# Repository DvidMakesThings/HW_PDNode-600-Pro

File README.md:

# PDNode-600 Pro  
## High-Performance USB PD Power Distribution Unit – 10" Rackmount

## Description  
[ENERGIS](https://github.com/DvidMakesThings/HW_10-In-Rack_PDU) is the 230V managed PDU project. PDNode-600 Pro is the modular DC/USB-C sibling for setups
where mains switching is not desired, but controllable, rack-friendly power output is still needed.

The PDNode-600 is a professional-grade, 600W USB Power Delivery Unit designed specifically for compact 10-inch rack systems, targeting embedded developers, homelab enthusiasts, test benches, and smart infrastructure. It delivers regulated, high-current power across 8x independent USB-C PD outputs and 4x fixed 5V USB-A outputs.

At the core of the PDNode platform is a centralized industrial-grade 24V/25A power supply, distributing regulated DC to dedicated per-port buck or buck-boost converters. Each USB-C port is managed by an MPQ4242-AEC1 PD controller, enabling clean, autonomous negotiation of power profiles up to 20V @ 3A or 5A with eMarker cable support. All power conversion, protection, and monitoring are designed to meet high reliability and safety standards.

The PDNode-600 Pro, by contrast, is built for remote-managed racks and headless environments, featuring Ethernet connectivity, a clean web-based UI, SNMP integration, and firmware updates via USB-C. Doing this by using [BladeCore-M54E](https://github.com/DvidMakesThings/HW_BladeCore-M54E)

## Web UI sneak peek

Interactive playground (dummy UI):
- https://dvidmakesthings.github.io/HW_PDNode-600-Pro/playground/

## Project timeline estimation

Status legend: ✅ Completed · 🟠 Ongoing · 🔵 Planned

| #  | Milestone                                      | Planned Start | Planned End | Status       | Notes |
|:--:|------------------------------------------------|---------------|-------------|--------------|-------|
| 1  | Architecture definition                        | 12-2025       | 01-2026     | ✅ Completed |       |
| 2  | Baseboard PCB design                           | 15-02-2026    | TBD         | ✅ Completed |       |
| 3  | PD card PCB design                             | 25-02-2026    | TBD         | ✅ Completed |       |
| 4  | Documentation                                  | 12-2025       | 2026.12     | 🟠 Ongoing   |       |
| 5  | PCB ordering                                   | 01-03-2026    | 31-03-2026  | ✅ Completed | Waiting for arrival |
| 6  | Prototyping and hardware bring-up              | 03-2026       | 30-04-2026  | 🟠 Ongoing   |       |
| 7  | Firmware bring-up (slot scan, mux, PD iface)   | 06-2026       | 11-2026     | 🔵 Planned   |       |
| 8  | Telemetry and status reporting                 | 06-2026       | 11-2026     | 🔵 Planned   |       |
| 9  | Validation (load, thermal, long-run)           | 06-2026       | 11-2026     | 🔵 Planned   |       |
| 10 | Integration and polishing                      | 06-2026       | 11-2026     | 🔵 Planned   |       |
| 11 | Release package and final docs                 | 11-2026       | 12-2026     | 🔵 Planned   |       |

## Specifications 

### Input
- **Input voltage:** 230 VAC, max 4A 
- **System topology:** 24V distribution on the baseboard, per-slot conversion on PD cards

### Output (per PD card / per slot)
- **8x independent USB-C PD source**:
  - 5V 3A (5A only with 5A e-marked cable)
  - 9V 3A (5A only with 5A e-marked cable)
  - 12V 3A (5A only with 5A e-marked cable)
  - 15V 3A (5A only with 5A e-marked cable)
  - 20V 3A (5A only with 5A e-marked cable)
  - (Total power output cannot exceed 600W)
- **4x USB-A source** up to **5V / 1A** per port (depending on configuration and limits)

---

## Features
- **8x independent USB-C PD source ports** (modular PD cards, one port per slot)
- **Per-port PD profiles**
- **Total system capability: up to 600W** (shared input power budget)
- **4x USB-A auxiliary outputs** (5V, 1A per port) for low-power devices
- **Ethernet connectivity** for control / monitoring
- **USB service interface** (debug, configuration, firmware update, or log access depending on implementation)
- **Per-port power monitoring** (current/voltage telemetry via onboard sensing)
- **Per-port status reporting** (PGOOD / fault indication, and software-readable status)
- **Hot-swappable slot concept** (cards can be replaced without redesigning the baseboard)

---

## Hardware architecture

### Baseboard
- 24V DC input from industrial power supply
- Power distribution to all slots (high-current bus)
- Slot connectors + slot management (card detect, enable, status aggregation)
- I2C fanout per slot (mux) for monitoring and controlling devices
- Ethernet interface for user interaction
- USB/service interface for debug/config/updates
- 4x USB-A outputs
- 8x USB-C PD outputs

### [BladeCore-M54E](https://github.com/DvidMakesThings/HW_BladeCore-M54E)
- RP2354B microcontroller
- External QSPI flash memory
- External I²C EEPROM
- 100BASE Ethernet via W5500
- Dual‑path USB connectivity with automatic source selection
- Onboard power regulation and defined power‑up sequencing
- Compact M.2 M-key form factor

### PD Card
- 1x USB-C PD source port (one card = one port)
- Local power conversion to generate VBUS from the 24V bus
- PD controller + USB-C port control signals (enable, reset, IRQ)
- Per-port current/voltage measurement
- Per-port power good / fault status output
- Optional ID EEPROM footprint (DNI) for traceability/calibration

## Schematics
The full schematics are available:
- **[Baseboard Schematics](src/PDF/SCH_PDNode_Baseboard_100.pdf)** 
- **[PDCard-4242 Schematics](src/PDF/SCH_PDCard-4242_100.pdf)**
- **[BladeCore-M54E Schematics](src/PDF/SCH_BladeCore-M54_100.pdf)**

PCB Documentation:
- **[Baseboard PCB](src/PDF/PCB_PDNode_Baseboard_100.pdf)** 
- **[PDCard-4242 PCB](src/PDF/PCB_PDCard-4242_100.pdf)**
 ****

---

## Development Phases (Hardware + Firmware)

| Hardware Phase                          | Status          | Firmware Phase                         | Status         |
| --------------------------------------- | --------------- | -------------------------------------- | -------------- |
| Architecture definition                 | ✅ Completed    | Slot scan concept (TCA9548A)           | 🔵 Planned     |
| Baseboard PCB Design                    | ✅ Completed    | I2C driver + mux control               | 🔵 Planned     |
| PD Card PCB Design                      | ✅ Completed    | INA219 monitoring                      | 🔵 Planned     |
| Documentation                           | 🟠 Ongoing      | PD controller interface (SPI + GPIO)   | 🔵 Planned     |
| PCB ordering                            | ✅ Completed    | Telemetry + status reporting           | 🔵 Planned     |
| Prototyping and Hardware Bring-up       | 🟠 Ongoing      | Bring-up scripts / debug tooling       | 🔵 Planned     |
| Validation (load, thermal, long-run)    | 🔵 Planned      | Error handling + fault reporting       | 🔵 Planned     |
| Production optimization                 | 🔵 Planned      | Integration and polishing              | 🔵 Planned     |

---

## Changelog 
#### Rev0.1.0:
- Initial design
- STUSB4710 controller + TPS552882

#### Rev1.0.0:
- Full redesign. STUSB4710 became EOL, need to use different PD controller
- New concept: modular Baseboard + PDCard architecture
- PDCard power stage (MPQ4242-AEC1)
- Baseboard: Per-slot I2C muxing (TCA9548A)
- Optional per-card EEPROM (not used, but capable)

<table>
  <tr>
    <td align="center">
      
      <br><b>PDCard Top</b>
    </td>
    <td align="center">
      
      <br><b>PDCard Bottom</b>
    </td>
  </tr>
  <tr>
    <td align="center" width="50%">
      
      <br><b>BladeCore-M54E Top</b>
    </td>
    <td align="center" width="50%">
      
      <br><b>BladeCore-M54E Bottom</b>
    </td>
  </tr>
  <tr>
    <td align="center">
      
      <br><b>BladeCore-M54E Top</b>
    </td>
    <td align="center">
      
      <br><b>BladeCore-M54E Bottom</b>
    </td>
  </tr>
</table>

## License
### Software Components
This project's software is licensed under the **GNU Affero General Public License v3.0 (AGPL-3.0)**.
See the [Software License](LICENSE-AGPL) file for details.

#### What AGPL-3.0 means:

- ✅ **You can** freely use, modify, and distribute this software
- ✅ **You can** use this project for personal, educational, or internal purposes
- ✅ **You can** contribute improvements back to this project

- ⚠️ **You must** share any modifications you make if you distribute the software
- ⚠️ **You must** release the source code if you run a modified version on a server that others interact with
- ⚠️ **You must** keep all copyright notices intact

- ❌ **You cannot** incorporate this code into proprietary software without sharing your source code
- ❌ **You cannot** use this project in a commercial product without either complying with AGPL or obtaining a different license

### Hardware Components
Hardware designs, schematics, and related documentation are licensed under the **Creative Commons Attribution-NonCommercial-ShareAlike 4.0 International License (CC BY-NC-SA 4.0 International License)**. See the [Hardware License](LICENSE-CC-BY-NC-SA) file for details.

#### What CC BY-NC-SA 4.0 means:

- ✅ **You can** study, modify, and distribute the hardware designs
- ✅ **You can** create derivative works for personal, educational, or non-commercial use
- ✅ **You can** build this project for your own personal use

- ⚠️ **You must** give appropriate credit and indicate if changes were made
- ⚠️ **You must** share any modifications under the same license terms
- ⚠️ **You must** include the original license and copyright notices

- ❌ **You cannot** use the designs for commercial purposes without explicit permission
- ❌ **You cannot** manufacture and sell products based on these designs without a commercial license
- ❌ **You cannot** create closed-source derivatives for commercial purposes
- ❌ **You cannot** use the designer's trademarks without permission

### Commercial & Enterprise Use

Commercial use of this project is prohibited without obtaining a separate commercial license. If you are interested in:

- Manufacturing and selling products based on these designs
- Incorporating these designs into commercial products
- Any other commercial applications

Please contact me through any of the channels listed in the [Contact](#contact) section to discuss commercial licensing arrangements. Commercial licenses are available with reasonable terms to support ongoing development.

## Contact

For questions or feedback:
- **Email:** [dvidmakesthings@gmail.com](mailto:dvidmakesthings@gmail.com)
- **GitHub:** [DvidMakesThings](https://github.com/DvidMakesThings)

## Contributing

Contributions are welcome! As this is an early-stage project, please reach out before 
making substantial changes:

1. Fork the repository
2. Create a feature branch (`git checkout -b feature/concept`)
3. Commit your changes (`git commit -m 'Add concept'`)
4. Push to the branch (`git push origin feature/concept`)
5. Open a Pull Request with a detailed description

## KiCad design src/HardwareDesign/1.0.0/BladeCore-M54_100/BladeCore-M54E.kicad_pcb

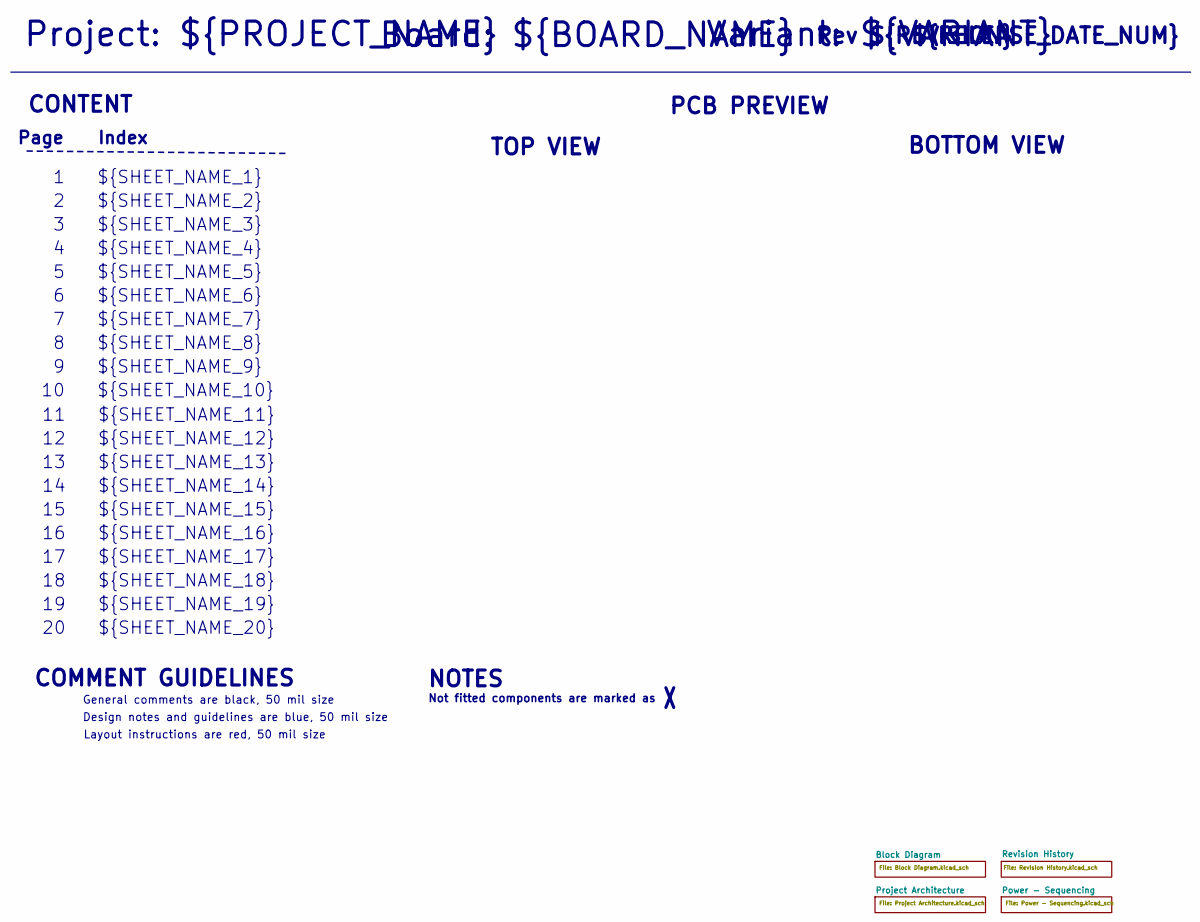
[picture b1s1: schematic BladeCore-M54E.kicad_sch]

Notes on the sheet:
${SHEET_NAME_12}
${SHEET_NAME_8}
${SHEET_NAME_2}
${SHEET_NAME_5}
${SHEET_NAME_20}
Page
PCB PREVIEW
${RELEASE_DATE_NUM}
CONTENT
${SHEET_NAME_11}
${SHEET_NAME_6}
Rev ${REVISION}
${SHEET_NAME_15}
BOTTOM VIEW
${SHEET_NAME_14}
${SHEET_NAME_17}
${SHEET_NAME_18}
${SHEET_NAME_7}
Not fitted components are marked as
Project: ${PROJECT_NAME}
NOTES
Design notes and guidelines are blue, 50 mil size
${SHEET_NAME_1}
${SHEET_NAME_9}
Board: ${BOARD_NAME}
General comments are black, 50 mil size
${SHEET_NAME_16}
${SHEET_NAME_3}
Variant: ${VARIANT}
${SHEET_NAME_19}
TOP VIEW
${SHEET_NAME_10}
Index
${SHEET_NAME_13}
${SHEET_NAME_4}
COMMENT GUIDELINES
Layout instructions are red, 50 mil size

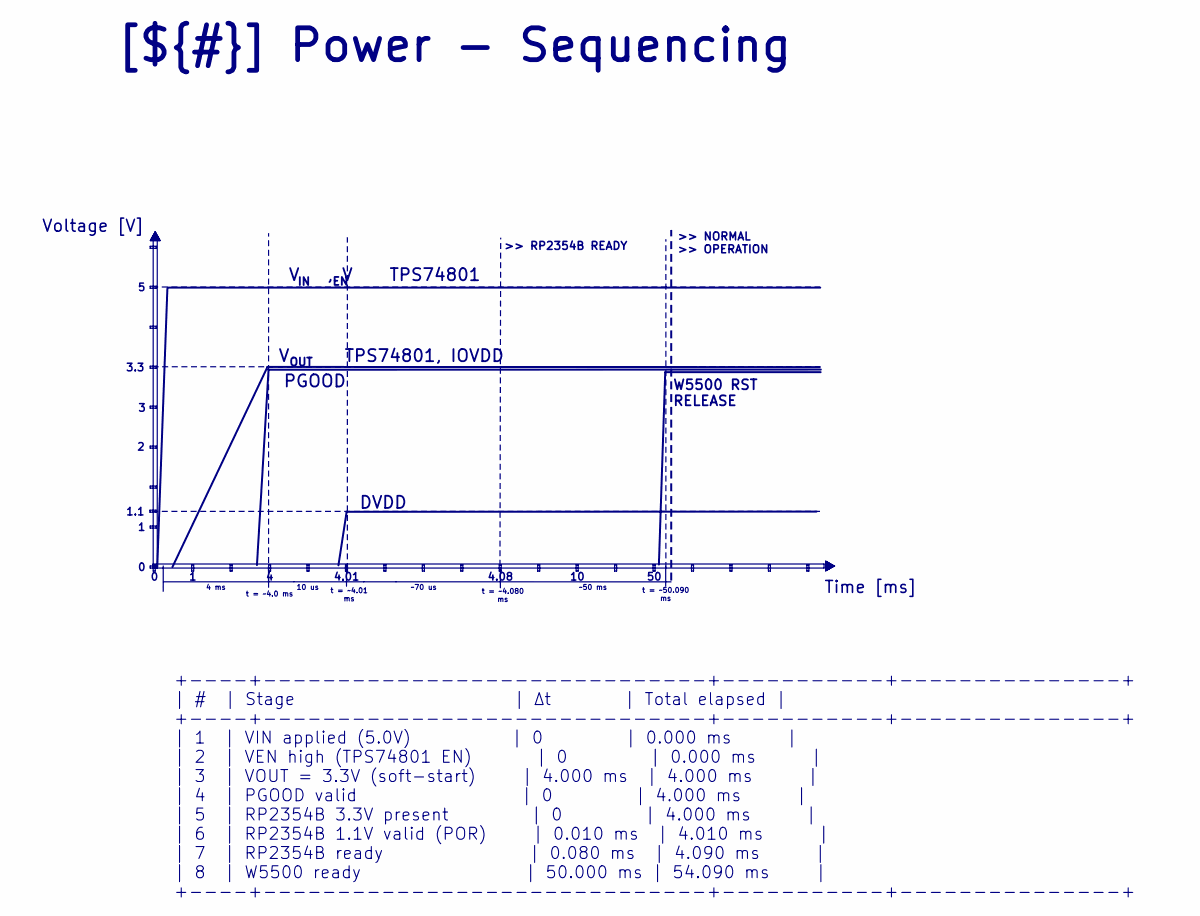
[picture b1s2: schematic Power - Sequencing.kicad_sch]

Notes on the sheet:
>> RP2354B READY
Voltage [V]
+----+------------------------------+-----------+---------------+ | # | Stage | Δt | Total elapsed | +----+------------------------------+-----------+---------------+ | 1 | VIN applied (5.0V) | 0 | 0.000 ms | | 2 | VEN high (TPS74801 EN) | 0 | 0.000 ms | | 3 | VOUT = 3.3V (soft-start) | 4.000 ms | 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
>> NORMAL >> OPERATION
Time [ms]
10 us
4.08
~70 us
4.01
DVDD
t = ~4.01 ms
3.3
W5500 RST RELEASE
~50 ms
t = ~50.090 ms
t = ~4.080 ms
V , V TPS74801
t = ~4.0 ms
PGOOD
1.1
4 ms
OUT
V TPS74801, IOVDD
[${#}] ${TITLE}

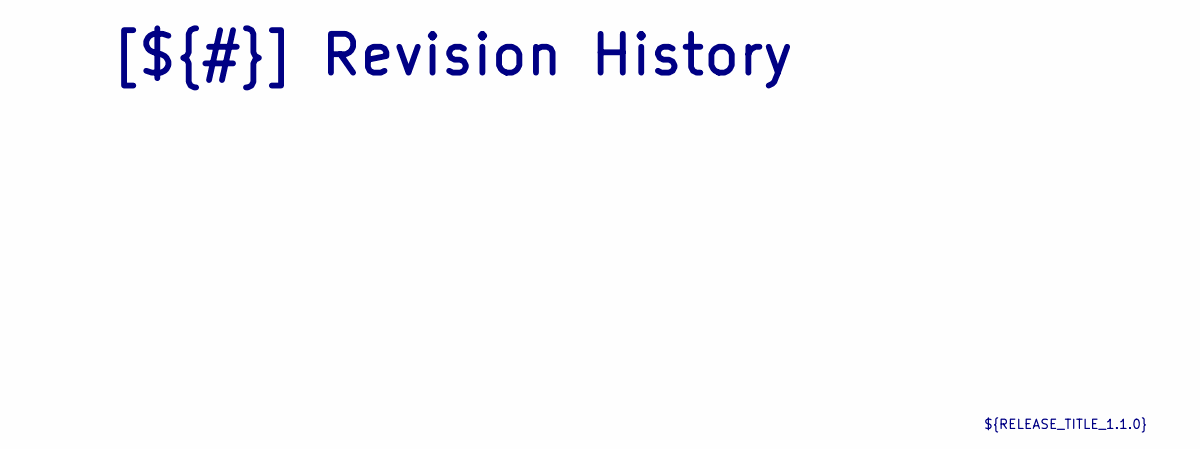
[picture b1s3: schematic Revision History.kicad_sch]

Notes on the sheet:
[${#}] ${TITLE}
${RELEASE_TITLE_1.1.0}

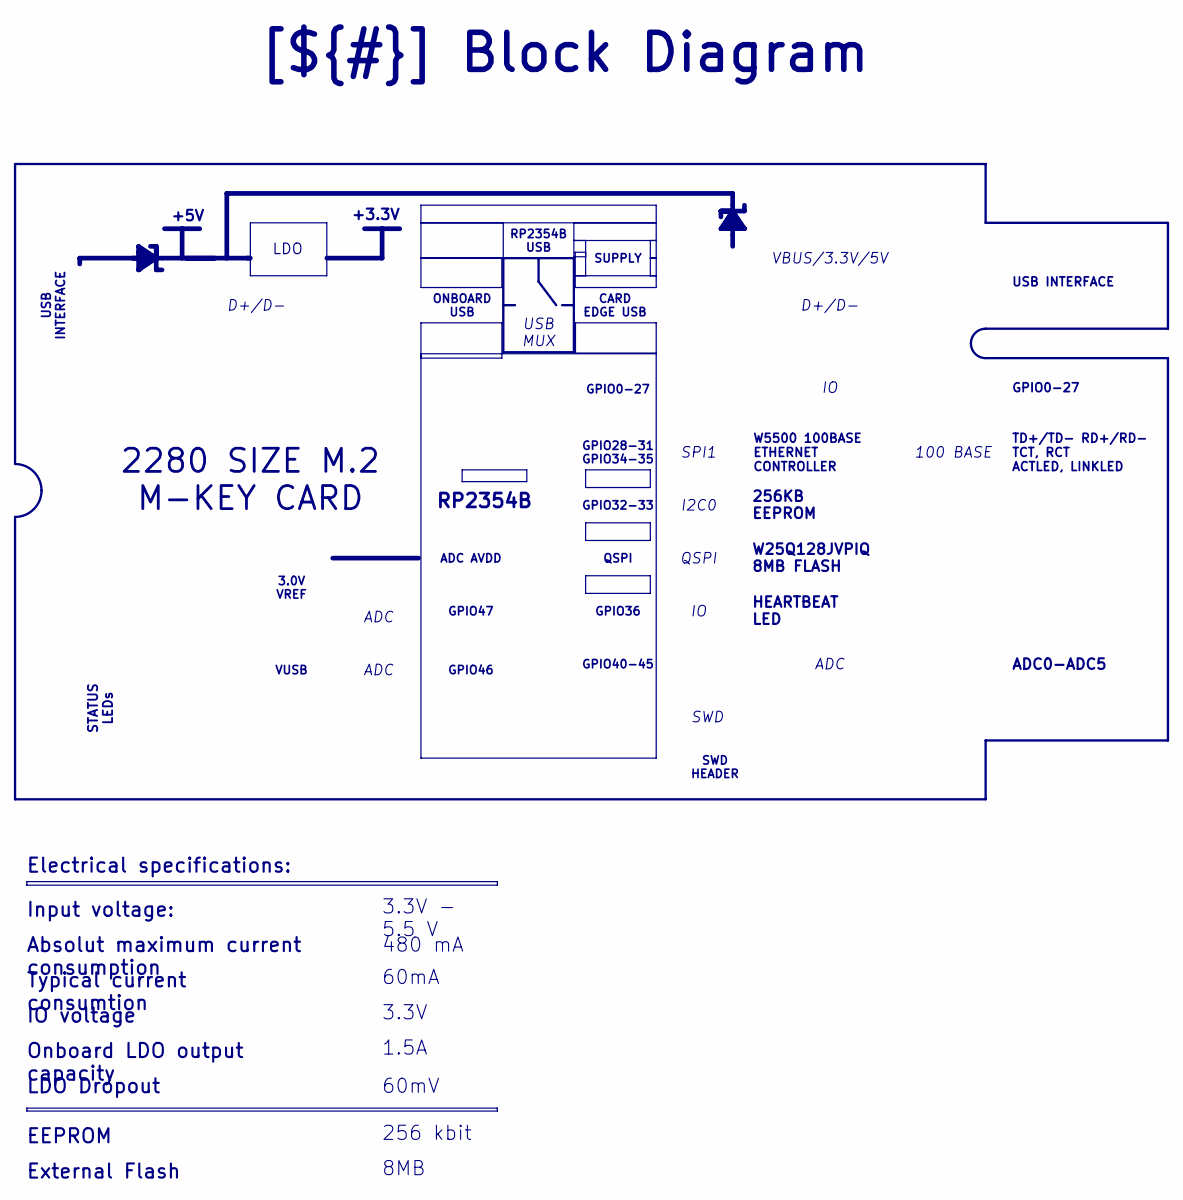
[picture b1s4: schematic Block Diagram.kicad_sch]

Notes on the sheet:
+3.3V
RP2354B
2280 SIZE M.2 M-KEY CARD
+5V
USB INTERFACE
LDO Dropout
IO voltage
256KB EEPROM
VBUS/3.3V/5V
1.5A
CARD EDGE USB
W25Q128JVPIQ 8MB FLASH
3.3V - 5.5 V
ADC0-ADC5
SWD HEADER
LDO
3.3V
GPIO0-27
TD+/TD- RD+/RD- TCT, RCT ACTLED, LINKLED
SPI1
W5500 100BASE ETHERNET CONTROLLER
GPIO40-45
ADC
QSPI
3.0V VREF
RP2354B USB
GPIO32-33
[${#}] ${TITLE}
480 mA
Input voltage:
STATUS LEDs
EEPROM
GPIO46
256 kbit
Electrical specifications:
SWD
GPIO47
GPIO36
GPIO28-31 GPIO34-35
ONBOARD USB

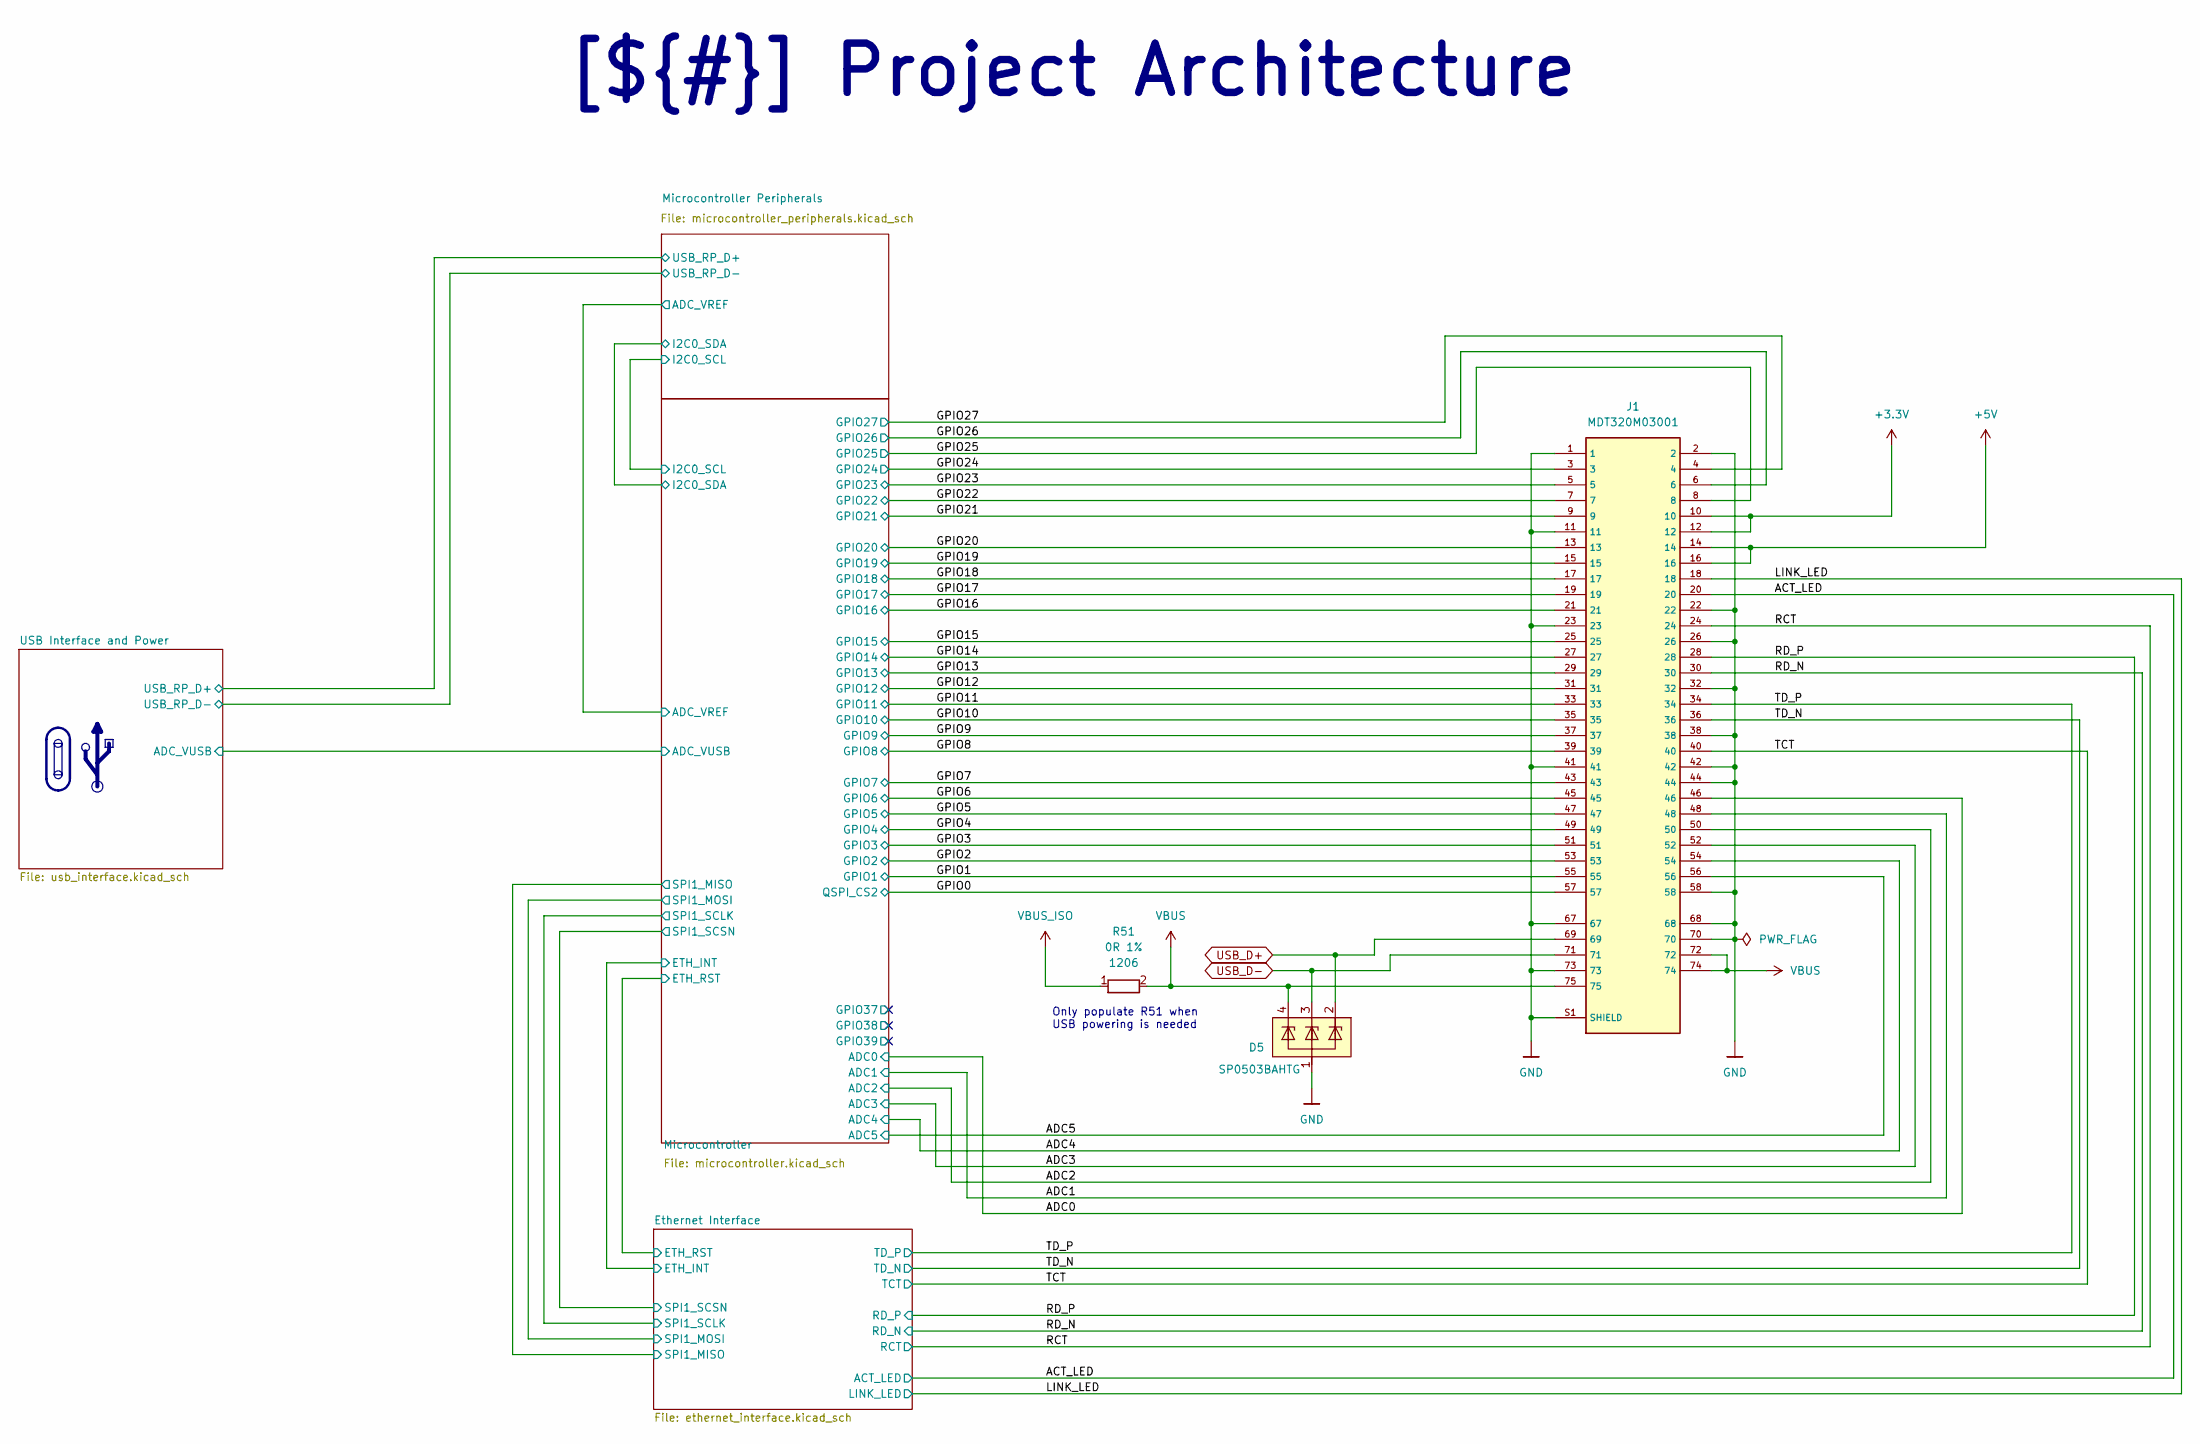
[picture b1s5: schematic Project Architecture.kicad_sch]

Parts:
D5: SP0503BAHTG; SOT143; MPN SP0503BAHTG; LCSC_PART C3040626
J1: MDT320M03001; M.2-M-KEY_Card_2280
R51: 0R 1%; R_1206_3216Metric; LCSC_PART C205296

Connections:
+3.3V: J1.10, J1.12; also elsewhere on the board
+5V: J1.14, J1.16; also elsewhere on the board
/Project Architecture/ACT_LED: J1.20; also elsewhere on the board
/Project Architecture/ADC0: J1.46; also elsewhere on the board
/Project Architecture/ADC1: J1.48; also elsewhere on the board
/Project Architecture/ADC2: J1.50; also elsewhere on the board
/Project Architecture/ADC3: J1.52; also elsewhere on the board
/Project Architecture/ADC4: J1.54; also elsewhere on the board
/Project Architecture/ADC5: J1.56; also elsewhere on the board
/Project Architecture/GPIO0: J1.57; also elsewhere on the board
/Project Architecture/GPIO1: J1.55; also elsewhere on the board
/Project Architecture/GPIO2: J1.53; also elsewhere on the board
/Project Architecture/GPIO3: J1.51; also elsewhere on the board
/Project Architecture/GPIO4: J1.49; also elsewhere on the board
/Project Architecture/GPIO5: J1.47; also elsewhere on the board
/Project Architecture/GPIO6: J1.45; also elsewhere on the board
/Project Architecture/GPIO7: J1.43; also elsewhere on the board
/Project Architecture/GPIO8: J1.39; also elsewhere on the board
/Project Architecture/GPIO9: J1.37; also elsewhere on the board
/Project Architecture/GPIO10: J1.35; also elsewhere on the board
/Project Architecture/GPIO11: J1.33; also elsewhere on the board
/Project Architecture/GPIO12: J1.31; also elsewhere on the board
/Project Architecture/GPIO13: J1.29; also elsewhere on the board
/Project Architecture/GPIO14: J1.27; also elsewhere on the board
/Project Architecture/GPIO15: J1.25; also elsewhere on the board
/Project Architecture/GPIO16: J1.21; also elsewhere on the board
/Project Architecture/GPIO17: J1.19; also elsewhere on the board
/Project Architecture/GPIO18: J1.17; also elsewhere on the board
/Project Architecture/GPIO19: J1.15; also elsewhere on the board
/Project Architecture/GPIO20: J1.13; also elsewhere on the board
/Project Architecture/GPIO21: J1.9; also elsewhere on the board
/Project Architecture/GPIO22: J1.7; also elsewhere on the board
/Project Architecture/GPIO23: J1.5; also elsewhere on the board
/Project Architecture/GPIO24: J1.3; also elsewhere on the board
/Project Architecture/GPIO25: J1.8; also elsewhere on the board
/Project Architecture/GPIO26: J1.6; also elsewhere on the board
/Project Architecture/GPIO27: J1.4; also elsewhere on the board
/Project Architecture/LINK_LED: J1.18; also elsewhere on the board
/Project Architecture/RCT: J1.24; also elsewhere on the board
/Project Architecture/RD_N: J1.30; also elsewhere on the board
/Project Architecture/RD_P: J1.28; also elsewhere on the board
/Project Architecture/TCT: J1.40; also elsewhere on the board
/Project Architecture/TD_N: J1.36; also elsewhere on the board
/Project Architecture/TD_P: J1.34; also elsewhere on the board
GND: D5.1, J1.1, J1.2, J1.11, J1.22, J1.23, J1.26, J1.32, J1.38, J1.41, J1.42, J1.44, J1.58, J1.67, J1.68, J1.70, J1.73, J1.S1 (SHIELD), J1.S2 (SHIELD); also elsewhere on the board
USB_D+: D5.2, J1.69; also elsewhere on the board
USB_D-: D5.3, J1.71; also elsewhere on the board
VBUS: D5.4, J1.72, J1.74, J1.75, R51.2; also elsewhere on the board
VBUS_ISO: R51.1; also elsewhere on the board

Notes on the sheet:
Only populate R51 when USB powering is needed
[${#}] ${TITLE}

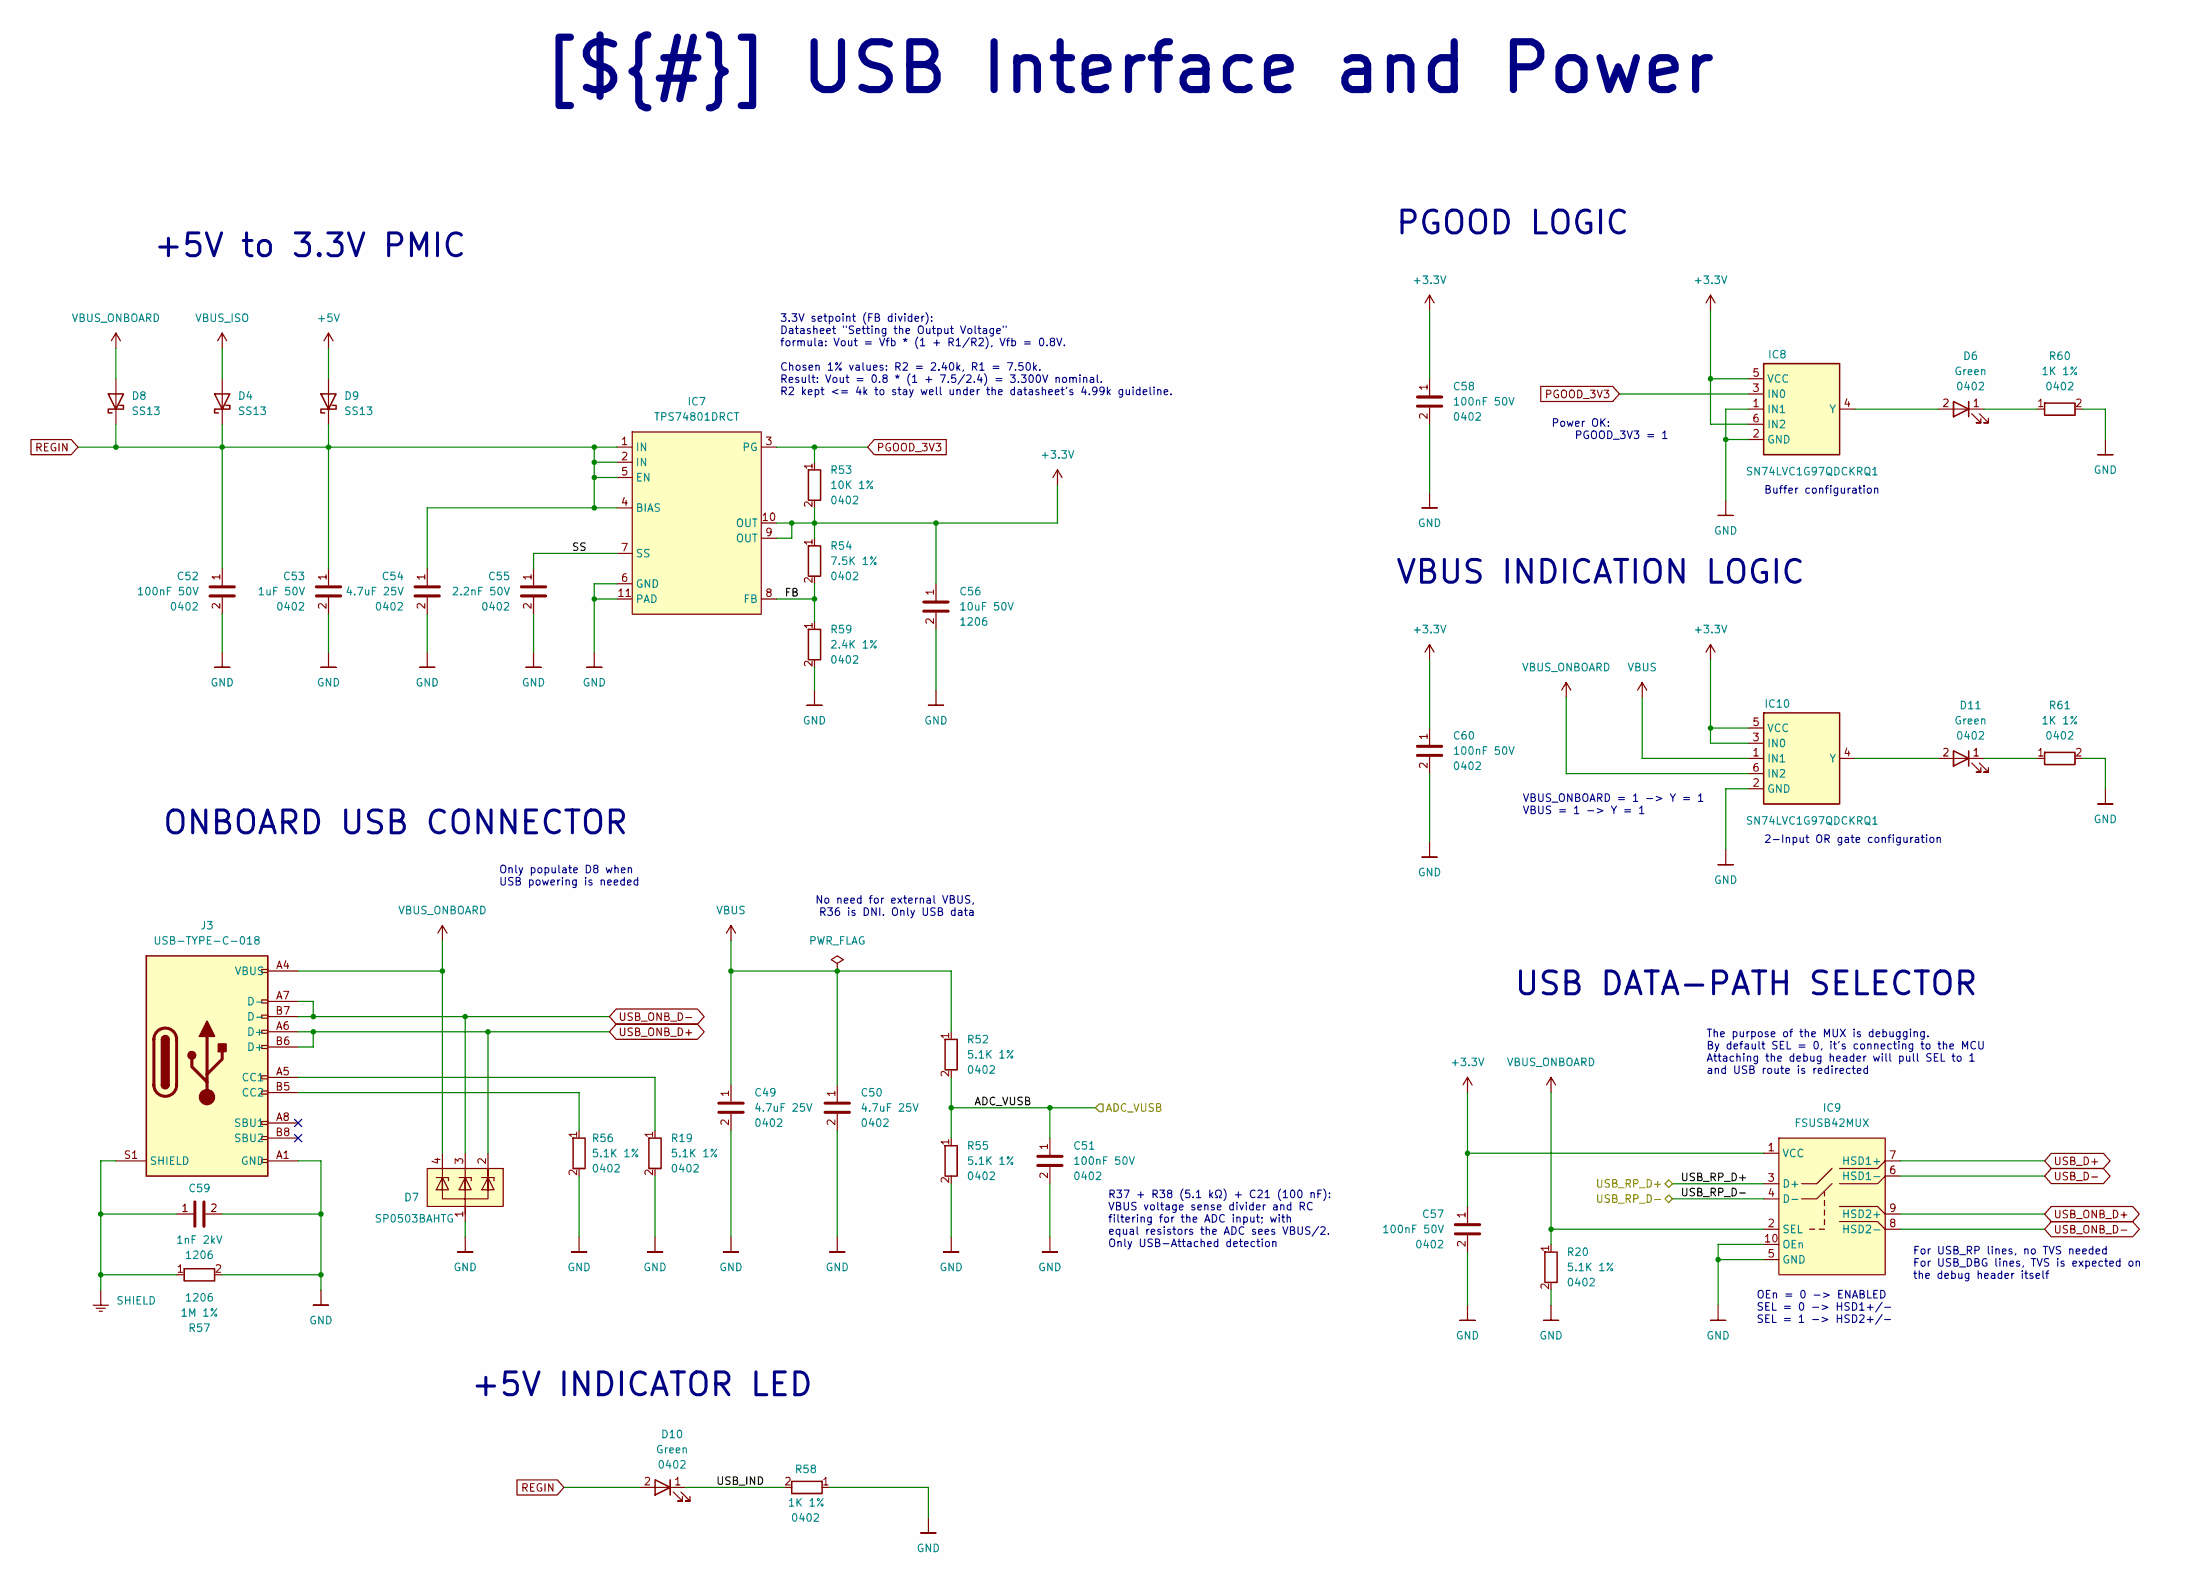
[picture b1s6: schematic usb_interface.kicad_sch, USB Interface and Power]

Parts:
C49, C50, C54: 4.7uF 25V; C_0402_1005Metric; LCSC_PART C22367824
C51, C52, C57, C58, C60: 100nF 50V; C_0402_1005Metric; LCSC_PART C307331
C53: 1uF 50V; C_0402_1005Metric; LCSC_PART C1518208
C55: 2.2nF 50V; C_0402_1005Metric; MPN CC0402KRX7R9BB222; LCSC_PART C106861
C56: 10uF 50V; C_1206_3216Metric; MPN CL31A106KBHNNNE; LCSC_PART C13585
C59: 1nF 2kV; C_1206_3216Metric; LCSC_PART C173242
D4, D8, D9: SS13; D_SMA
D6, D10, D11: Green; LED_0402_1005Metric; MPN XL-1005UGC; LCSC_PART C965793
D7: SP0503BAHTG; SOT143; MPN SP0503BAHTG; LCSC_PART C3040626
IC7: TPS74801DRCT; VSON-10-1EP_3x3mm_P0.5mm_EP1.65x2.4mm_ThermalVias; MPN TPS74801DRCT; LCSC_PART C882845
IC8, IC10: SN74LVC1G97QDCKRQ1; SOT-363_SC-70-6; MPN SN74LVC1G97QDCKRQ1; LCSC_PART C179911
IC9: FSUSB42MUX; MSOP-10_3x3mm_P0.5mm; MPN FSUSB42MUX; LCSC_PART C11355
J3: USB-TYPE-C-018; USB_C_Receptacle_HCTL_HC-TYPE-C-16P-01A; MPN USB-TYPE-C-018; LCSC_PART C2927038
R19, R20, R52, R55, R56: 5.1K 1%; R_0402_1005Metric; LCSC_PART C25905
R53: 10K 1%; R_0402_1005Metric; LCSC_PART C25744
R54: 7.5K 1%; R_0402_1005Metric; LCSC_PART C25918
R57: 1M 1%; R_1206_3216Metric; LCSC_PART C17927
R58, R60, R61: 1K 1%; R_0402_1005Metric; LCSC_PART C11702
R59: 2.4K 1%; R_0402_1005Metric; LCSC_PART C25882

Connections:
+3.3V: C56.1, C57.1, C58.1, C60.1, IC7.9 (OUT), IC7.10 (OUT), IC8.5 (VCC), IC8.6 (IN2), IC9.1 (VCC), IC10.3 (IN0), IC10.5 (VCC), R53.2, R54.1; also elsewhere on the board
+5V: D9.2 (A); also elsewhere on the board
/Project Architecture/Microcontroller/ADC_VUSB: C51.1, R52.2, R55.1; also elsewhere on the board
/Project Architecture/USB Interface and Power/FB: IC7.8 (FB), R54.2, R59.1
/Project Architecture/USB Interface and Power/SS: C55.1, IC7.7 (SS)
/Project Architecture/USB Interface and Power/USB_IND: D10.1, R58.2
/Project Architecture/USB Interface and Power/USB_RP_D+: IC9.3 (D+); also elsewhere on the board
/Project Architecture/USB Interface and Power/USB_RP_D-: IC9.4 (D-); also elsewhere on the board
GND: C49.2, C50.2, C51.2, C52.2, C53.2, C54.2, C55.2, C56.2, C57.2, C58.2, C59.2, C60.2, D7.1, IC7.6 (GND), IC7.11 (PAD), IC8.1 (IN1), IC8.2 (GND), IC9.5 (GND), IC9.10 (OEn), IC10.2 (GND), J3.A1 (GND), J3.A12 (GND), J3.B1 (GND), J3.B12 (GND), R19.2, R20.2, R55.2, R56.2, R57.2, R58.1, R59.2, R60.2, R61.2; also elsewhere on the board
unnamed: D6.1, R60.1
unnamed: D11.1, R61.1
unnamed: D6.2, IC8.4 (Y)
unnamed: D11.2, IC10.4 (Y)
unnamed: J3.A5 (CC1), R19.1
unnamed: J3.B5 (CC2), R56.1
PGOOD_3V3: IC7.3 (PG), IC8.3 (IN0), R53.1
REGIN: C52.1, C53.1, C54.1, D4.1 (K), D8.1 (K), D9.1 (K), D10.2, IC7.1 (IN), IC7.2 (IN), IC7.4 (BIAS), IC7.5 (EN)
SHIELD: C59.1, J3.S1 (SHIELD), R57.1
USB_D+: IC9.7 (HSD1+); also elsewhere on the board
USB_D-: IC9.6 (HSD1-); also elsewhere on the board
USB_ONB_D+: D7.2, IC9.9 (HSD2+), J3.A6 (D+), J3.B6 (D+)
USB_ONB_D-: D7.3, IC9.8 (HSD2-), J3.A7 (D-), J3.B7 (D-)
VBUS: C49.1, C50.1, IC10.1 (IN1), R52.1; also elsewhere on the board
VBUS_ISO: D4.2 (A); also elsewhere on the board
VBUS_ONBOARD: D7.4, D8.2 (A), IC9.2 (SEL), IC10.6 (IN2), J3.A4 (VBUS), J3.A9 (VBUS), J3.B4 (VBUS), J3.B9 (VBUS), R20.1

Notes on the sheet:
VBUS INDICATION LOGIC
OEn = 0 -> ENABLED SEL = 0 -> HSD1+/- SEL = 1 -> HSD2+/-
USB DATA-PATH SELECTOR
No need for external VBUS, R36 is DNI. Only USB data
2-Input OR gate configuration
+5V to 3.3V PMIC
+5V INDICATOR LED
3.3V setpoint (FB divider): Datasheet "Setting the Output Voltage" formula: Vout = Vfb * (1 + R1/R2), Vfb = 0.8V. Chosen 1% values: R2 = 2.40k, R1 = 7.50k. Result: Vout = 0.8 * (1 + 7.5/2.4) = 3.300V nominal. R2 kept <= 4k to stay well under the datasheet's 4.99k guideline.
ONBOARD USB CONNECTOR
For USB_RP lines, no TVS needed For USB_DBG lines, TVS is expected on the debug header itself
R37 + R38 (5.1 kΩ) + C21 (100 nF): VBUS voltage sense divider and RC filtering for the ADC input; with equal resistors the ADC sees VBUS/2. Only USB-Attached detection
VBUS_ONBOARD = 1 -> Y = 1 VBUS = 1 -> Y = 1
Power OK: PGOOD_3V3 = 1
Buffer configuration
PGOOD LOGIC
Only populate D8 when USB powering is needed
The purpose of the MUX is debugging. By default SEL = 0, it's connecting to the MCU Attaching the debug header will pull SEL to 1 and USB route is redirected
[${#}] ${TITLE}
